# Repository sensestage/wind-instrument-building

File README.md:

# wind-instrument-building
Files for wind instrument building workshops

## Linz workshop (June 2022)

In this workshop we use an ESP32-S2 board to send data from self-made sensors and a motion sensor (MPU6050) via WiFi and OSC. This data can be received by e.g. Processing, SuperCollider, or Puredata, or MobMuPlatform (Pd on a phone).

- [presentation slides](https://marijebaalman.eu/Downloads/workshops/wind-instrument-building-linz.pdf)

## Taipei workshop (May 2022)

In this workshop we use the [Sense/Stage MiniBee](https://sensestage.eu/minibee) to receive data from self-made sensors on kites, as well as the onboard accelerometer.

For presentation slides:

- [day 1 - making sensors](https://marijebaalman.eu/Downloads/workshops/wind-instrument-building-taipei-day1.pdf)
- [day 2 - receiving and viewing data](https://marijebaalman.eu/Downloads/workshops/wind-instrument-building-taipei-day2.pdf)
- [day 3 - processing and using data](https://marijebaalman.eu/Downloads/workshops/wind-instrument-building-taipei-day3.pdf)

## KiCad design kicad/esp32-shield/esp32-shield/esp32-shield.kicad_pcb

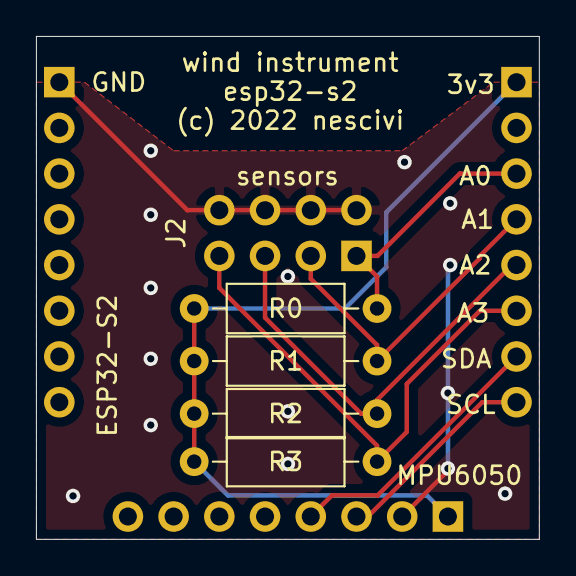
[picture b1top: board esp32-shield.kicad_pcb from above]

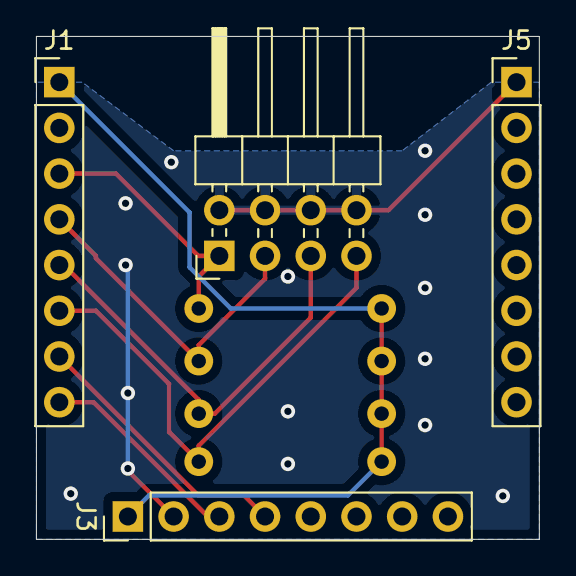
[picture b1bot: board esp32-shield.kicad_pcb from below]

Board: 2 copper layers, 27.9 x 27.9 mm, 8 parts (4 on the bottom side), 8 nets.

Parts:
J1, J5: ESP32-S2; PinHeader_1x08_P2.54mm_Vertical
J2: sensors; PinHeader_2x04_P2.54mm_Horizontal
J3: MPU6050; PinHeader_1x08_P2.54mm_Vertical
R0, R1, R2, R3: R_Small; R_Axial_DIN0207_L6.3mm_D2.5mm_P10.16mm_Horizontal

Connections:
+3V3: J1.1, J3.1, R0.1, R1.1, R2.1, R3.1
/A0: J1.3, J2.1, R0.2
/A1: J1.4, J2.3, R1.2
/A2: J1.5, J2.5, R2.2
/A3: J1.6, J2.7, R3.2
/SCL: J1.8, J3.3
/SDA: J1.7, J3.4
GND: J2.2, J2.4, J2.6, J2.8, J3.2, J5.1

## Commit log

2022-05-10 minibee configurations for workshop in Taipei
2022-05-10 processing sketch to view the data from the minibee
2022-05-10 add supercollider files to view data
2022-05-10 update processing sketch, add processing sketch for processing data
2022-05-10 example for connecting to data via xosc
2022-05-11 basic configuration for kites
2022-05-11 fixes for visualisation
2022-05-11 configuration for kite set 5
2022-05-11 visualizing remote data with processing
2022-05-11 add link to presentation slides for day 1
2022-05-11 add comment about port
2022-05-11 update the data processing sketch
2022-05-11 extension of the data processing sketch with sound triggers
2022-05-11 stop the plotter after use
2022-05-11 configuration file with the 6 different minibees connected to workshop host's computer
2022-05-11 add links to the new slides
2022-05-12 update to the data processing sketches
2022-05-12 add processing sketch that also plottes the processed data
2022-06-06 add Arduino files for ESP32-S2
2022-06-06 kicad ESP32-S2 olimex shield design
2022-06-13 add version with html webserver (not working yet)
2022-06-13 basic code for unit (static webname and oscport)
2022-06-16 update supercollider files
2022-06-16 images for sensor construction
2022-06-16 MobMuPlat files
2022-06-16 firmware version with configuration possible of ssid and udp port
2022-06-16 firmware to clean the EEPROM. This needs to be uploaded and run once to make the firmware work for storing settings
2022-06-16 image of the pcb shield
2022-06-17 update gui of cosmic select patch
2022-06-17 addition of mobmuplat patches
2022-06-17 add missing files mobmuplat
2022-08-27 add link to slides in readme

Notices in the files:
kicad/esp32-shield/esp32-shield/esp32-shield.kicad_pcb:
(c) 2022 nescivi
